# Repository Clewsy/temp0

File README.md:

# temp0
A temperature/humidity sensor that provides live readings over WiFi and via an oled display.
The device connects to a local network over WiFi and serves the following:
- Pretty html page at root:
	- http://temp0
- Simple text only temperature value at:
	- http://temp0/temperature
	- http://temp0/temp
	- http://temp0/t
- Simple text only humidity value at:
	- http://temp0/humidity
	- http://temp0/humi
	- http://temp0/h

The code was developed using the [PlatformIO][link_web_platformio] extension in [VSCode][link_web_vscode].  The hardware was designed using [KiCAD][link_web_kicad] and fabricated using [JLCPCB][link_web_jlcpcb].

All components are on a custom PCB and inside an enclosure with a transperant lid so as to show off the special-edition [HackADay 10-year anniversary Pro Trinket][link_web_hackaday_pro_trinket]!

More info can be found [here][link_clews_projects_temp0].

## Goals
This project was developed to meet a few goals:
- Create a device for monitoring internal temperature - to be compatible with automation platforms (specifically [Home Assistant][link_web_home_assistant]).
	- Local temperature read-out.
	- Simple web-server for obtaining temperature over WiFi.
	- Simple text-only response when calling a specific url with curl (also over WiFi). 
- Make use of - and potentially showcase - a special [HackADay 10-year anniversary edition Pro-Trinket][link_web_hackaday_pro_trinket] dev board.
- Learn how to use an [esp8266][link_web_esp8266].
- Try out [arduino][link_web_arduino] (instead of directly programming microcontrollers).
	- Try the [arduino IDE][link_web_arduino_ide] and programming via the arduino bootloader.
	- Try using some [C++][link_wiki_c++] for development instead of just [C][link_wiki_c].

## Components
The final system consists of the following components:
- [Pro Trinket 5V][link_repo_data_pro_trinket] (Hackaday 10-Year Anniversary Special-Edition) - Controls the SSD1306 and the HDC1080. Sends temperature/humidity readings over serial to the ESP8266 module.
- [ESP8266][link_repo_data_esp8266] (ESP-01 module) - Acts as a web-server to provide temperature/humidity over WiFi.
- [HDC1080][link_repo_data_hdc1080] module - Temperature/Humidity sensor that communicates over I2C.
- [SSD1306][link_repo_data_ssd1306] OLED module - also communicates over I2C - used as a local display for temperature/humidity readings.
- Miscellaneous components for power conversion (5V->3.3V), filtering, IO pull-ups, etc.

## Repository
This repo contains:
- [data][link_repo_temp0_data] - datasheets I referenced to write relevant code and create custom [KiCAD][link_web_kicad] footprints.
- [images][link_repo_temp0_images] - photos of the final project.
- [temp0_esp8266][link_repo_temp0_esp8266] - code written for the ESP8266/ESP-01 module.
- [temp0_pro_trinket][link_repo_temp0_pro_trinket] - code written for the Pro Trinket module.
- [temp0_schematic][link_repo_temp0_schematic] - [KiCAD][link_web_kicad] files including the schematic and PCB layout.  Library includes some custom parts (ESP-01, Pro-Trinket, HDC1080, OLED).
- [temp0_workspace.code-workspace][link_repo_temp0_workspace] - Workspace structure for VSCode including PlatformIO configurations for working with the ESP8266/ESP-01 and the Pro-Trinket 5V.

## Gallery
### Start-up animation.
![Demo of startup][image_temp0_demo_startup]

### Cycling through different display modes.
![Demo of display modes][image_temp0_demo_modes]

### Assembled PCB.
![Assembled unit][image_temp0_assembled]

### In an enclosure.
![Buttoned up][image_temp0_complete]

### Web interface.
![WebUI][image_temp0_webui]

[link_clews_projects_temp0]:https://clews.pro/projects/temp0.php

[link_repo_temp0_data]:/data
[link_repo_data_esp8266]:/data/esp8266_pinout.png
[link_repo_data_hdc1080]:/data/hdc1080_i2c_temperature_humidity_sensor.pdf
[link_repo_data_pro_trinket]:/data/pro_trinket_5V_pinout.jpeg
[link_repo_data_ssd1306]:/data/ssd1306_oled_driver.pdf

[link_repo_temp0_esp8266]:/temp0_esp8266
[link_repo_temp0_images]:/images
[link_repo_temp0_pro_trinket]:/temp0_pro_trinket
[link_repo_temp0_schematic]:/temp0_schematic
[link_repo_temp0_workspace]:/temp0_workspace.code-workspace

[link_web_arduino]:https://www.arduino.cc/
[link_web_arduino_ide]:https://www.arduino.cc/en/Main/Software
[link_web_esp8266]:http://esp8266.net/
[link_web_hackaday_pro_trinket]:https://hackaday.com/2014/10/10/10th-anniversary-trinket-pro-now-in-the-hackaday-store/
[link_web_home_assistant]:https://www.home-assistant.io/
[link_web_jlcpcb]:https://jlcpcb.com/
[link_web_kicad]:https://kicad.org/
[link_web_platformio]:https://platformio.org/
[link_web_vscode]:https://code.visualstudio.com/

[link_wiki_c]:https://en.wikipedia.org/wiki/C_(programming_language)
[link_wiki_c++]:https://en.wikipedia.org/wiki/C%2B%2B

[image_temp0_assembled]:/images/temp0_assembled.jpg
[image_temp0_complete]:/images/temp0_complete.jpg
[image_temp0_demo_modes]:/images/temp0_demo_modes.gif
[image_temp0_demo_startup]:/images/temp0_demo_startup.gif
[image_temp0_webui]:/images/temp0_webui.png

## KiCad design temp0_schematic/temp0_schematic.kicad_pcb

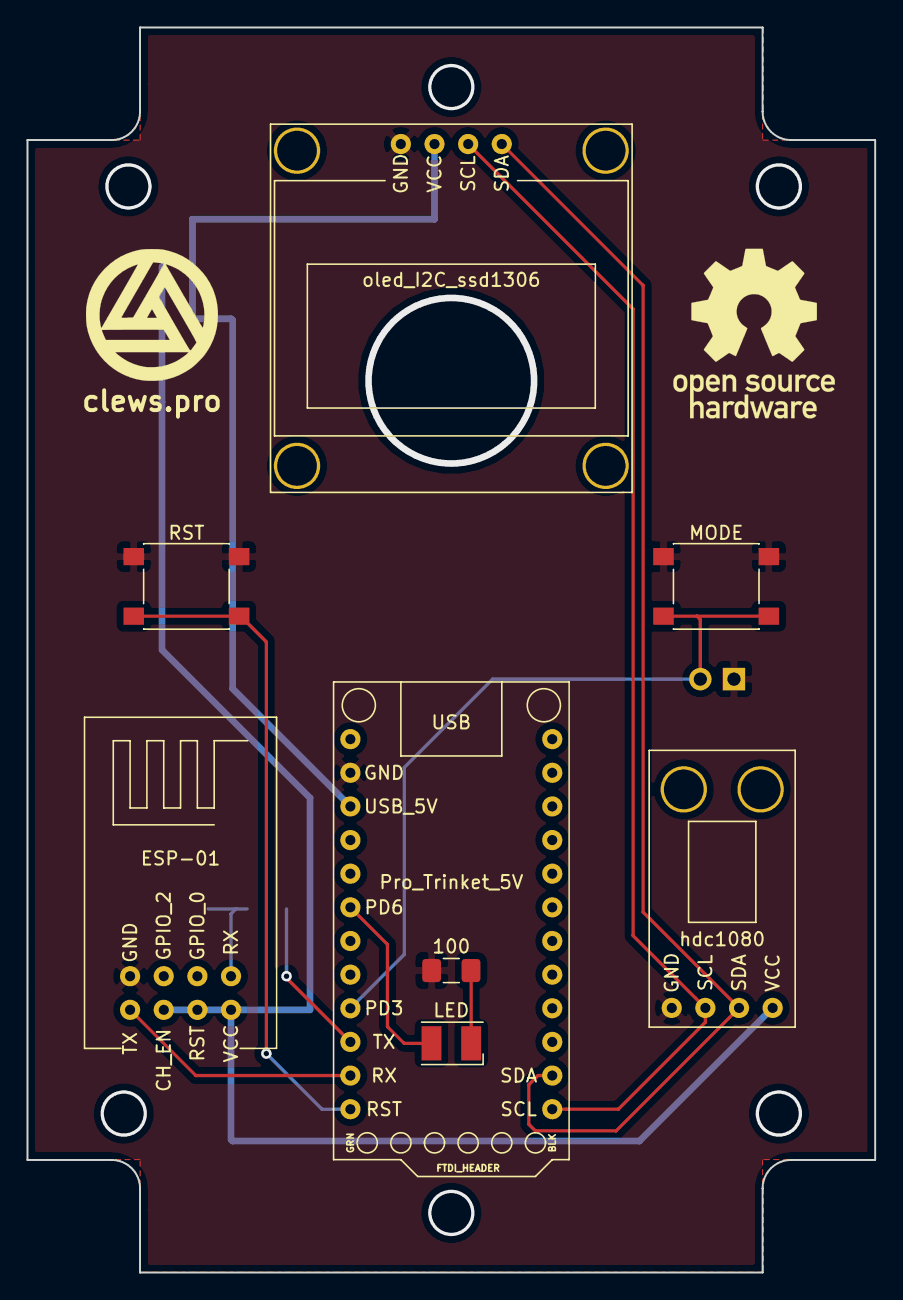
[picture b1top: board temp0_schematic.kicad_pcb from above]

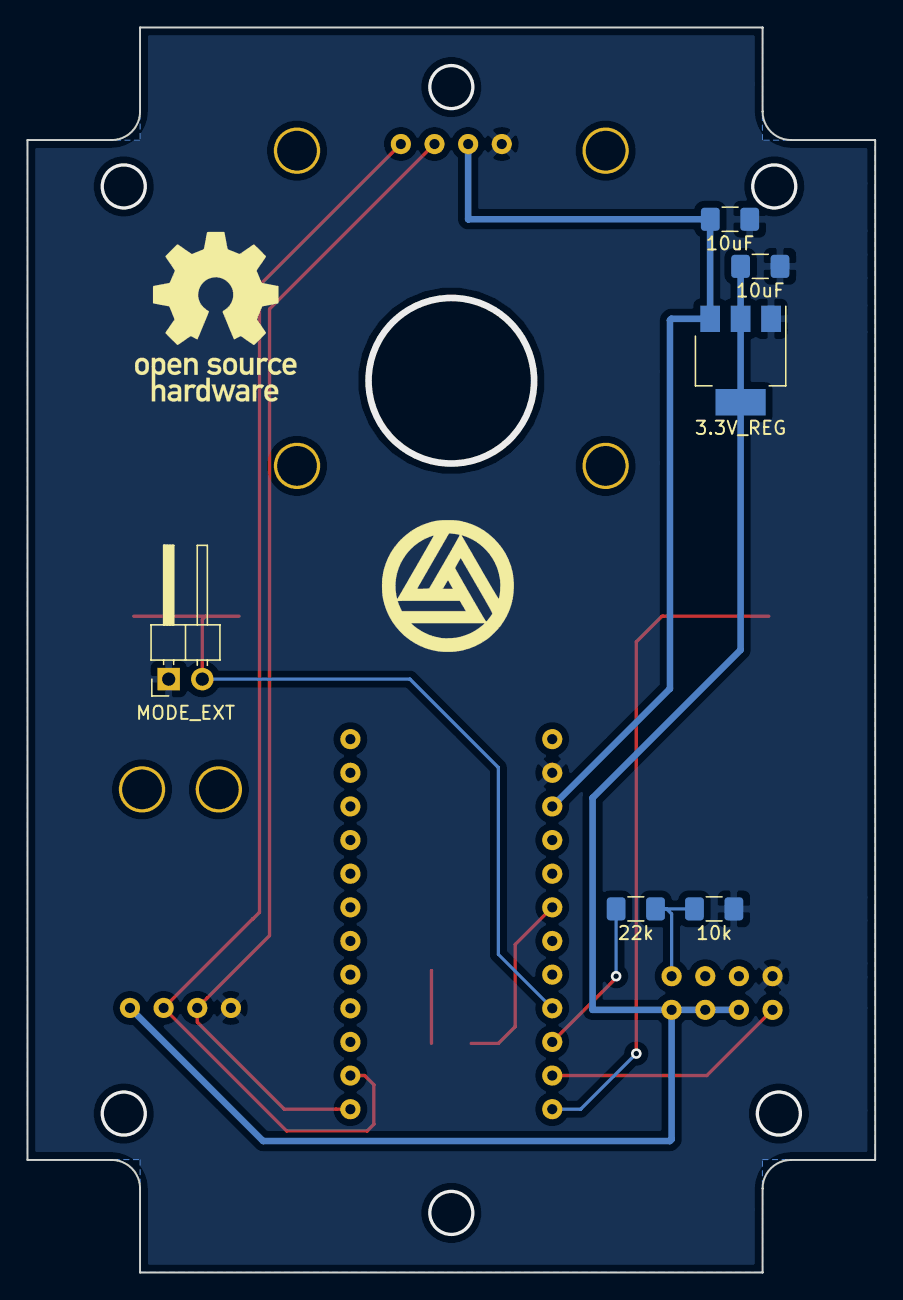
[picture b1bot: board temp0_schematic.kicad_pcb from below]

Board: 2 copper layers, 64.0 x 94.0 mm, 14 parts (6 on the bottom side), 12 nets.

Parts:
C1, C2: 10uF; C_1206_3216Metric_Pad1.42x1.75mm_HandSolder
D1: LED; LED_PLCC-2
J1: MODE_EXT; PinHeader_1x02_P2.54mm_Horizontal
MODE: SW_Push; SW_Push_1P1T_NO_6x6mm_H9.5mm
R1: 100; R_1206_3216Metric_Pad1.42x1.75mm_HandSolder
R3: 10k; R_1206_3216Metric_Pad1.42x1.75mm_HandSolder
R4: 22k; R_1206_3216Metric_Pad1.42x1.75mm_HandSolder
RST: SW_Push; SW_Push_1P1T_NO_6x6mm_H9.5mm
U1: Pro_Trinket_5V
U2: ESP-01
U3: oled_I2C_ssd1306; oled_i2c_ssd1306
U4: hdc1080
U5: 3.3V_REG; SOT-223-3_TabPin2

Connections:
3.3V: C2.1, U2.4, U2.6, U2.8, U4.4, U5.2
5V: C1.1, U1.3, U3.2, U5.3
GND: C1.2, C2.2, J1.1, MODE.1, R1.2, R3.2, RST.1, U1.2, U2.1, U3.1, U4.1, U5.1
unnamed: D1.1, R1.1
unnamed: D1.2, U1.6
unnamed: J1.2, MODE.2, U1.9
unnamed: R3.1, R4.2, U2.7
unnamed: RST.2, U1.12
SCL: U1.24, U3.3, U4.2
SDA: U1.23, U3.4, U4.3
U1_RX: U1.11, U2.2
U1_TX: R4.1, U1.10

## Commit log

2020-03-08 Init git and first commit. Still experimenting. ESP8266 and trinket talking via serial.
2020-03-08 Reading in temp and humidity from hdc180.
2020-03-08 Learning the ++ part of C++.
2020-03-08 It's working! Temperature and humidity webserver.
2020-03-08 Clean-up.
2020-03-09 Added a favicon to the web server main page.
2020-03-09 HTML prettification.
2020-03-09 Added hostname. Other improvements.
2020-03-21 Working on oled ssd1306 driver and kicad schematic.
2020-03-22 Improved hdc1080 driver and implemented self-heat capability.
2020-03-22 Comments.
2020-03-22 Improvements, can print to oled now.
2020-03-22 Use splash screen duration to run heater. Remove unused fonts.
2020-03-24 Implemented a push-button with de-bounce on a hardware interrupt - will eventually control display modes.
2020-03-25 Attempted prettification of html output. Added newline to end of plain-text outputs.
2020-03-28 Broke functions out of main. Added output LED.
2020-03-28 Added larger font and second display mode.
2020-03-28 Second display mode implementation.
2020-03-29 Working on the schematic and pcb (KiCad).
2020-03-29 Working on the schematic. Added header for external button.
2020-03-30 Ran traces.
2020-03-30 Completed first attempt at pcb. Generated gerbers to order fab.
2020-03-31 PCB fixed - mount hole alignment, ftdi clearance, other.
2020-04-03 Fixed oled initialisation - now enables internal regulator.
2020-04-04 Tidied schematic and added pdf to repo.
2020-04-04 Tidied comments.
2020-04-04 Increased i2c speed.
2020-04-04 Cleaned up workspace.
2020-04-04 Cleaned up fonts.
2020-04-04 Improved clear_screen function - now faster.
2020-04-05 Added inverted oled display modes. Added external led pulse.
2020-04-05 Comment consistency.
2020-04-05 Beginning an overhaul of the fonts and typing system.
2020-04-05 Making progress with fonts overhaul.
2020-04-06 Omg fonts look great now.
2020-04-06 Improvements to character printing.
2020-04-06 Comments and legibility.
2020-04-06 Fixed LED puls (internal timer with overflo interrupt) centered large font display mode.
2020-04-11 Typos and comments.
2020-04-11 Improved string printing. Improved fonts. Added additional display modes.
2020-04-11 Edited comments. Changed interrupt init order.
2020-04-11 Added screen_invert function. Moved some oled functions from public to private.
2020-04-11 Typo.
2020-04-11 Restructured for readability.
2020-04-11 Comments and formatting.
2020-04-11 Formatting.
2020-04-12 Removed delay()s.
2020-04-12 Tweaks to box drawing. Added sensor read delay back in.
2020-04-18 Flipped oled display for installation on PCB rev2.
2020-04-18 Schematic and PCB revision 2.
2020-04-18 Removed .vscode dirs from repo.
2020-04-18 Formatting and typos.
2020-04-19 Removed redundant variables.
2020-04-19 Merged reset function into init function.
2020-04-19 Renamed some varaibles.
2020-04-19 Comment.
2020-04-19 Added rev2 schematic pdf.
2020-04-19 Added vscode workspace to repo.
2020-04-21 Added readme.
2020-04-28 Added ability to display 128x64 image.
2020-04-29 Added second logo.
2020-05-02 Improved LED pulse function.
2020-05-02 Added blank screen mode, added function to enable/disable pulsing LED.
2020-05-03 Added temperature bodge, updated readme, added photos.
2020-05-03 Readme formatting, added webui image.
2020-05-03 Updated readme.
2020-05-03 Added license.
2020-05-30 Dimmed pulse LED. Changed display mode ordering.
2020-06-12 Rotated photos, added embedded bitmaps and info.
2020-06-12 Typos.
2020-06-12 Extra note.
2020-06-28 Consolidated clear_screen into map_bits function and improved efficiency/speed. General code tidy for consistency and readability.
2020-06-28 Added links.
2020-09-15 Improved box drawing function. Removed pointless display modes.
2020-09-15 Improved box drawing function. Added comments.
2020-09-16 Various adjustments.
2021-11-10 Update README.md https://forum.kicad.info/t/warning-avoid-all-links-to-kicad-pcb-org-use-kicad-org/31521
2022-05-01 Reprogramming for new network. Just did some comment tidy-up.
2022-05-01 Slightly simpler.
